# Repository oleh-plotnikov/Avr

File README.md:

Programm and PCB EagleCAD project files for microprocessor local cooling for solar panels. Cooling method: active, air flow. A device with a digital temperature measurement sensor (DS18b20) and a microprocessor (ATiny 13A) to enable / disable cooling system continuously comparing the measured temperature with preset constants.

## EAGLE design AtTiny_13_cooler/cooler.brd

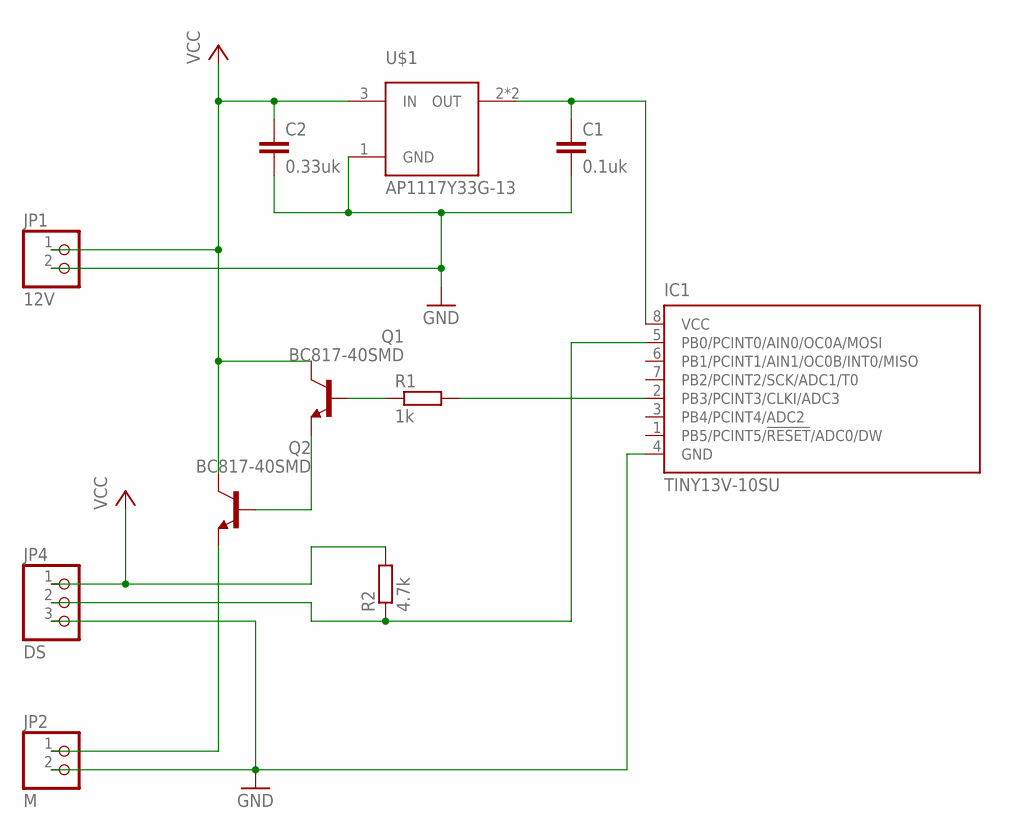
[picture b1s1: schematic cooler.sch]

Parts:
C1: 0.1uk; C0805
C2: 0.33uk; C0805
IC1: TINY13V-10SU; 8S2
JP1: 12V; 1X02/90
JP2: M; 1X02/90
JP4: DS; 1X03/90
Q1, Q2: BC817-40SMD; SOT23-BEC
R1: 1k; R0805
R2: 4.7k; R0805
U$1: AP1117Y33G-13; SOT89

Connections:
GND: C1.2, C2.2, IC1.4 (GND), JP1.2, JP2.2, JP4.3, U$1.1 (GND)
unnamed: C1.1, IC1.8 (VCC), U$1.2 (OUT), U$1.2@1 (OUT)
unnamed: JP2.1, Q2.E
unnamed: Q1.E, Q2.B
unnamed: Q1.B, R1.1
unnamed: IC1.2 (PB3/PCINT3/CLKI/ADC3), R1.2
unnamed: IC1.5 (PB0/PCINT0/AIN0/OC0A/MOSI), JP4.2, R2.1
VCC: C2.1, JP1.1, JP4.1, Q1.C, Q2.C, R2.2, U$1.3 (IN)

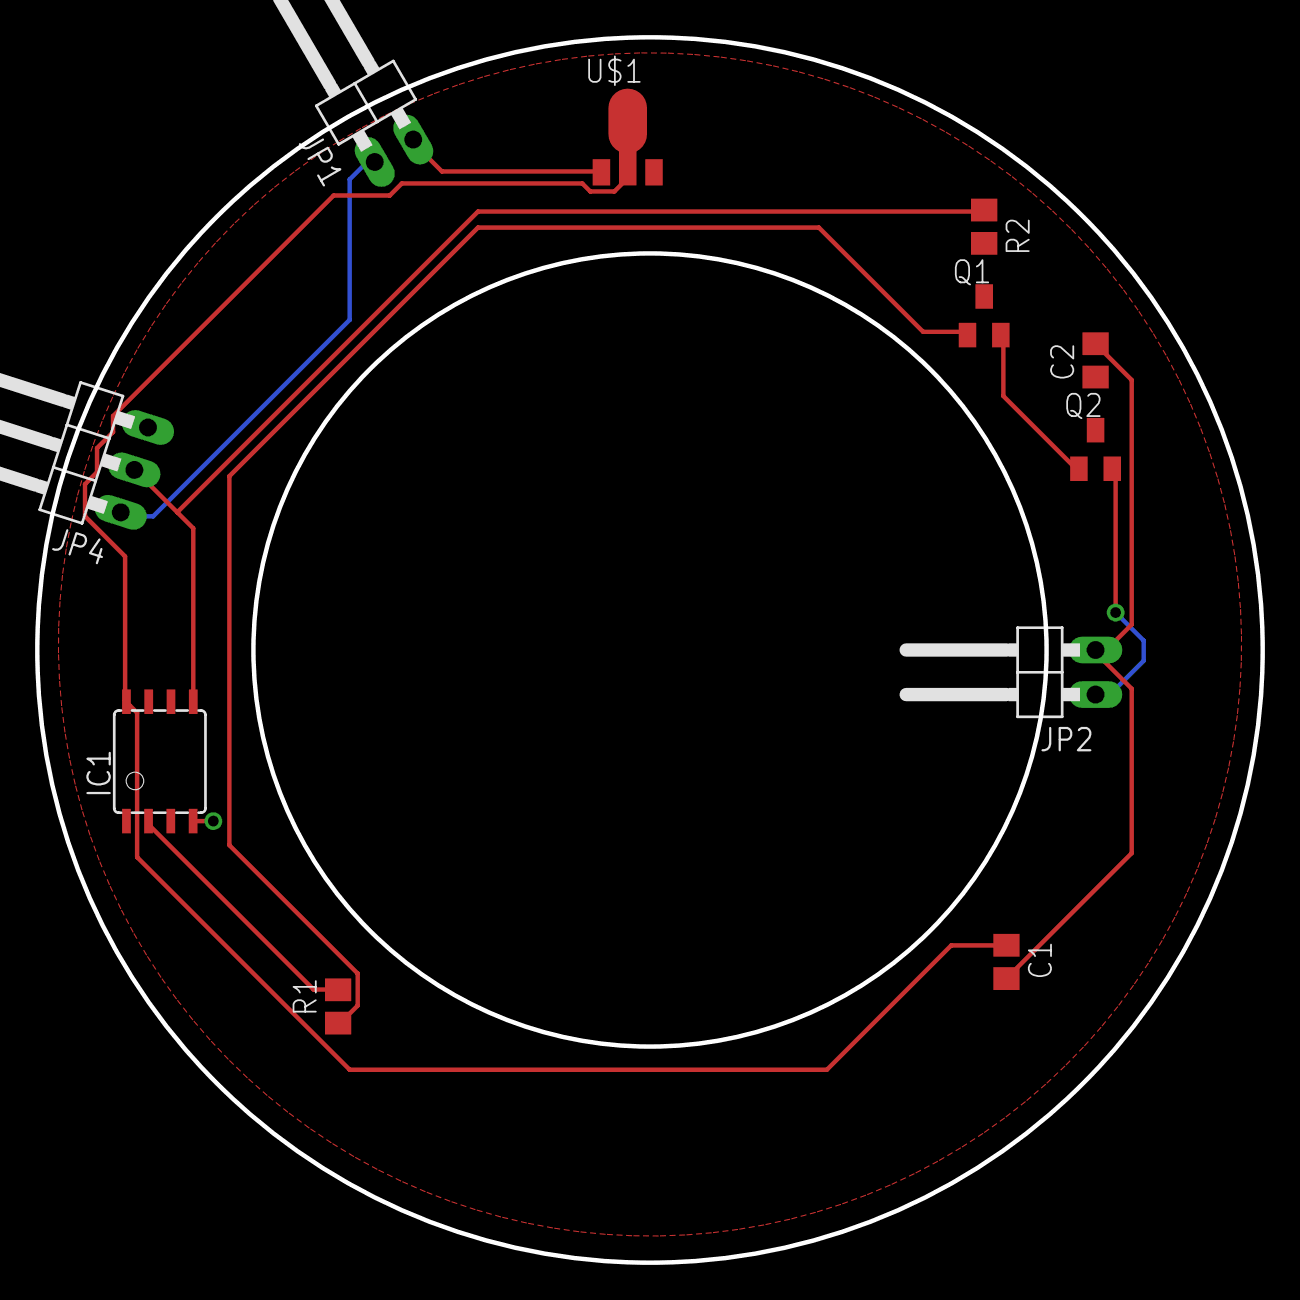
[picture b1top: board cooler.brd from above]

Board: 2 copper layers, 69.9 x 69.9 mm, 11 parts (0 on the bottom side), 8 nets.
